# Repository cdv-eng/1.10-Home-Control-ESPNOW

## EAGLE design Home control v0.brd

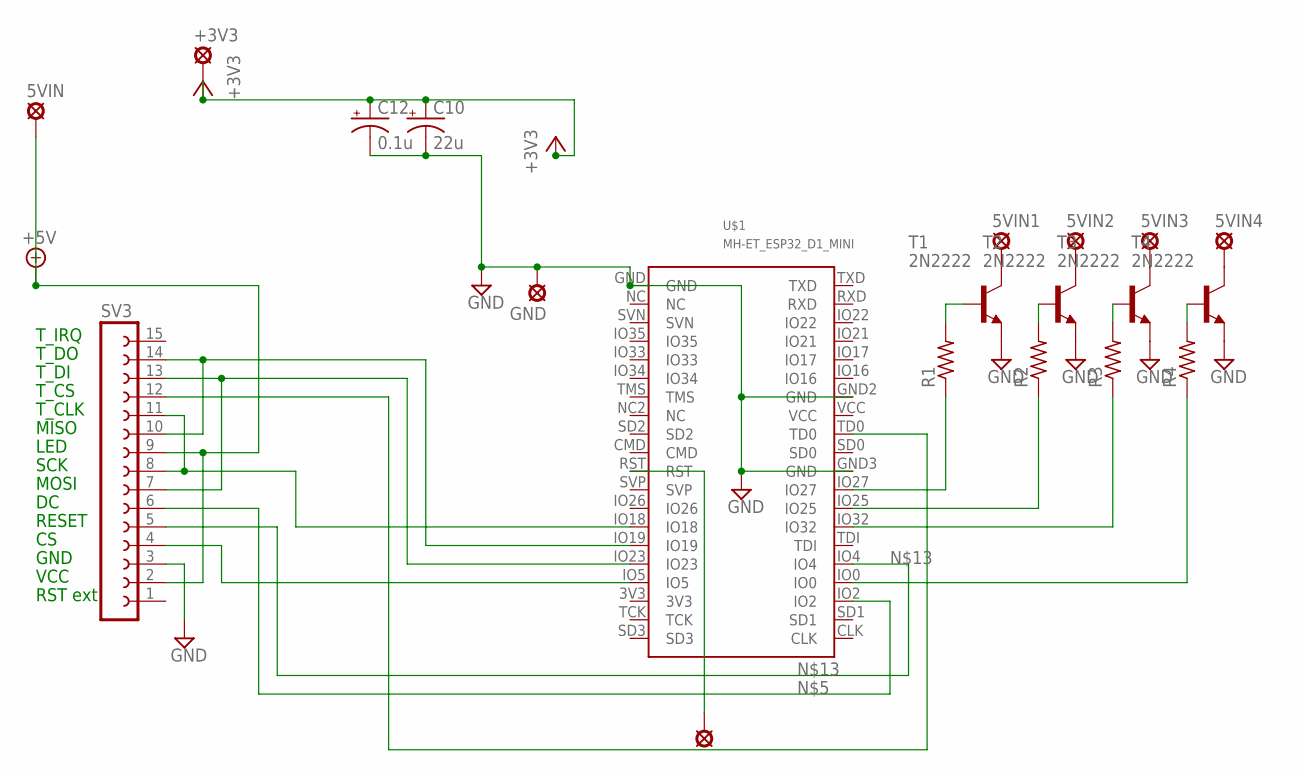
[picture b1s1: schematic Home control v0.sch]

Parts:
5VIN, 5VIN1, 5VIN2, 5VIN3, 5VIN4: LSP10
+3V3: LSP10
C10: 22u; E3,5-8
C12: 0.1u; E2-5
GND: LSP10
R1, R2, R3, R4: R-US_R0603; R0603
RST: LSP10
SV3: FE15-1; FE15
T1, T2, T3, T4: 2N2222; TO92-EBC-OVAL
U$1: MH-ET_ESP32_D1_MINI

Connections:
+3V3: +3V3.MP, C10.+, C12.+
+5V: 5VIN.MP, SV3.2, SV3.9
GND: C10.-, C12.-, GND.MP, SV3.3, T1.E, T2.E, T3.E, T4.E, U$1.GND, U$1.GND2 (GND), U$1.GND3 (GND)
unnamed: R1.2, T1.B
unnamed: SV3.10, SV3.14, U$1.IO19
unnamed: SV3.7, SV3.13, U$1.IO23
unnamed: R2.2, T2.B
unnamed: SV3.6, U$1.IO2
unnamed: SV3.12, U$1.TD0
unnamed: R3.2, T3.B
unnamed: SV3.8, SV3.11, U$1.IO18
unnamed: R4.2, T4.B
unnamed: SV3.4, U$1.IO5
unnamed: R1.1, U$1.IO27
unnamed: R2.1, U$1.IO25
unnamed: SV3.5, U$1.IO4
unnamed: R3.1, U$1.IO32
unnamed: 5VIN1.MP, T1.C
unnamed: 5VIN2.MP, T2.C
unnamed: 5VIN3.MP, T3.C
unnamed: 5VIN4.MP, T4.C
unnamed: R4.1, U$1.IO0
unnamed: RST.MP, U$1.RST

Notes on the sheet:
T_IRQ
T_DO
T_DI
T_CS
T_CLK
MISO
LED
SCK
MOSI
RESET
GND
VCC
RST ext

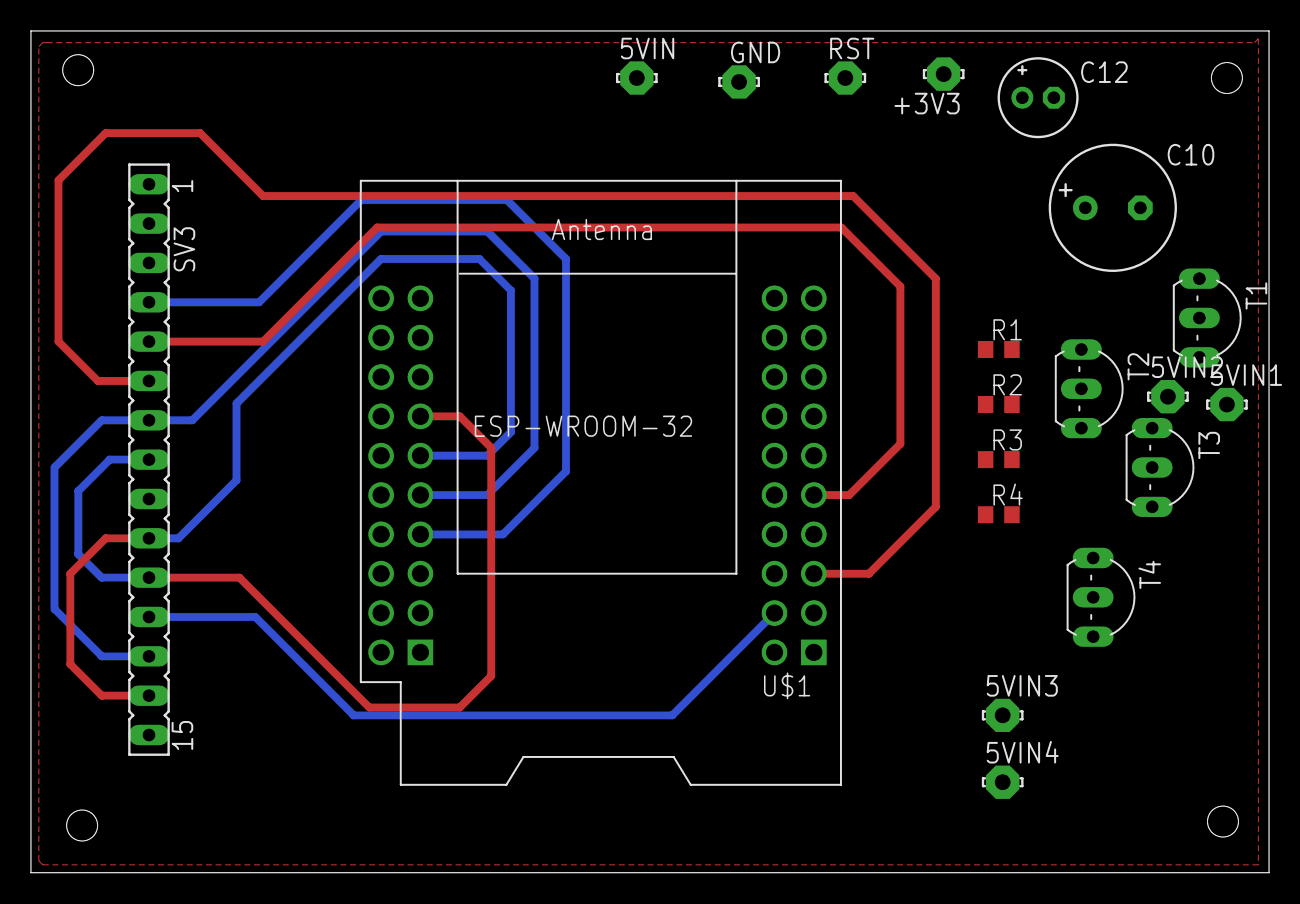
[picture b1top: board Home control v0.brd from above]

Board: 2 copper layers, 79.9 x 54.3 mm, 20 parts (0 on the bottom side), 23 nets.
